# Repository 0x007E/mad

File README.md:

# `MAD` - Matrix Display

The `MAD` project is based on a pcb with an [ATtiny406/ATtiny1606](#additional-information) and a [Matrix LED Display](#additional-information). It can be used to display data sent over `SPI` or `UART`. The display also implements a small amount of characters from the ASCII table and also has internal space (`EEPROM`) for 16 special characters that can be programmed.

| Experience | Level |
|:------------|:-----:|
| Soldering   |  |
| Mechanical  |  |
| Software    |  |

# Downloads

| Type      | File               | Description              |
|:---------:|:------------------:|:-------------------------|
| Schematic | [pdf](https://github.com/0x007E/mad/releases/latest/download/schematic.pdf) / [cadlab](https://cadlab.io/project/28600/main/files) | Schematic files |
| Board | [pdf](https://github.com/0x007E/mad/releases/latest/download/pcb.pdf) / [cadlab](https://cadlab.io/project/28600/main/files) | Board file |
| Drill | [pdf](https://github.com/0x007E/mad/releases/latest/download/drill.pdf) | Drill file |
| PCB | [zip](https://github.com/0x007E/mad/releases/latest/download/kicad.zip) / [tar](https://github.com/0x007E/mad/releases/latest/download/kicad.tar.gz) | KiCAD/Gerber/BoM/Drill files |
| Mechanical | [zip](https://github.com/0x007E/mad/releases/latest/download/freecad.zip) / [tar](https://github.com/0x007E/mad/releases/latest/download/freecad.tar.gz) | FreeCAD/Housing and PCB (STEP) files     |
| Firmware | [zip](https://github.com/0x007E/mad/releases/latest/download/firmware.zip) / [tar](https://github.com/0x007E/mad/releases/latest/download/firmware.tar.gz) | Firmware for ATtiny406/ATtiny1606 (Display) |
| Firmware (demo) | [zip](https://github.com/0x007E/mad/releases/latest/download/firmware-demo.zip) / [tar](https://github.com/0x007E/mad/releases/latest/download/firmware-demo.tar.gz) | Test application(s) for ATmega16a |

# Hardware

There are two parts of the hardware. The pcb and the housing of the `MAD`. The pcb is created with [KiCAD](#additional-information) and the housing with `FreeCAD`. The software is programmed with [Microchip (Atmel) Studio](#additional-information). All files are built with `github actions` so that they are ready for a production environment. The housing is printed with a 3D-printer (`Dremel 3D40`).

## PCB

The circuit board is populated on both sides (Top, Bottom). The best way for soldering the `SMD` components is within a vapor phase soldering system and for the `THT` components with a standard soldering system.

### Top Layer

### Bottom Layer

## Mechanical

The housing has a tolerance of `0.2mm` on each side of the case. So the pcb should fit perfectly in the housing. The tolerance can be modified with `FreeCAD` in the `Parameter` Spreadsheet.

### Assembled

#### Exploded

# Programming/Setup

The `MAD` is powerd with `5V` from an external source. With Jumper `JP1` bridged the `MAD` can be programmed over [UPDI](#additional-information). To enable `UART` mode the `SS (CS)` Pin must be held low (more details on the [dataflow](#dataflow-diagram) diagram) otherwise the `SPI` mode is enabled. In `UART` mode only one display can be driven. The `SI` pin gets `TXD`and the `SO` pin gets `RXD`. The firmware for the display can be downloaded (see the [download section](#downloads)).

``` bash
#         +-+                                         +----------+      +---------------------+
#        / /                                          |   U  +---+---+  |                     |
#      +-+-+-----------------+                        |   S  |  USB  |--+ +-----------------+ |
#      | JP1                 |                        |   B  +---+---+  | | AVR-Dude        | |
#      |    MAD - Display    |       +---------+      |   /      |      | | ~~~~~~~~        | |
#    +-+-+                 +-+-+   +-+-+  U    |      |   U      |      | | ~~~~~           | |
#    | 1 | VCC         VCC | 1 +---+VCC|  P  +-+-+  +-+-+ A      |      | | ~~~~~~~~~~~~    | |
#    | 2 | UPDI       UPDI | 2 +---+PDI|  D  |GND+--+GND| R      |      | |                 | |
#    | 3 | SI           SO | 3 |   +-+-+  I  |VCC+--+VCC| T      |      | +-----------------+ |
#    | 4 | SCK         SCK | 4 |     |       +---+  +---+ A      |      |                     |
#    | 5 | SS (CS)      SS | 5 +   +-+-+     |RxD+--+RxD| +------+      | Computer            |
#    | 6 | GND         GND | 6 +---+GND|     |TxD+--+TxD| |5V/3V3|      |                     |
#    +-+-+                 +-+-+   +-+-+     +-+-+  +-+-+ +------+      +---------------------+
#      +---------------------+       | ADAPTER |      +----+-----+
#                                    +---------+
```

## FUSES

| Register  | Value  |
|:---------:|:------:|
| `WDTCFG`  | `0x00` |
| `BODCFG`  | `0x00` |
| `OSCCFG`  | `0x02` |
| `TCD0CFG` | `0x00` |
| `SYSCFG0` | `0xF5` |
| `SYSCFG1` | `0x00` |
| `APPEND`  | `0x00` |
| `BOOTEND` | `0x00` |

> To setup `SW1` as `RESET` (`PA0`) it is necessary to change the `SYSCFG0`-FUSE of the `ATtiny406/ATtiny1606`. WARNING: To reset the `PA0` pin to `UPDI` mode a `12V` impulse is necessary to program the FUSES again.

# Software

The display software can be controlled by `SPI` or `UART`. The interfaces are displayed in the [dataflow](#dataflow-diagram) diagram. There is a demo software to use the display directly over `spi` (`MAD_Test`) or a `library` (`MAD_LIB`).

## Dataflow diagram

## UART Test

To send characters to the display over `UART` connect an USB/UART converter to the PC and make a bridge beween `GND` and `SS (CS)` before powering up the display. Start a terminal software on the computer (e.g. [Teraterm](#additional-information)) and setup the following settings:

| Name      | Value  |
|:---------:|:------:|
| PORT      | COM?   |
| BAUD      | 9600   |
| DATABITS  | 8      |
| PARITY    | NONE   |
| STOPBITS  | 1      |
| FLOWCTRL  | NONE   |

### Connection setup

``` bash

#      +---------------------+                                +---------------------+
#      |    MAD - Display    |                                |                     |
#    +-+-+                 +-+-+                              | +-----------------+ |
#    | 1 | VCC         VCC | 1 +-------+    +----------+      | | TeraTerm        | |
#    | 2 | UPDI       UPDI | 2 |       |    |   U  +---+---+  | | ~~~~~~~~        | |
#    | 3 | SI           SO | 3 +-----+ |    |   S  |  USB  |--+ | ~~~~~           | |
#    | 4 | SCK         SCK | 4 |     | |    |   B  +---+---+  | | ~~~~~~~~~~~~    | |
#    | 5 | SS (CS)      SS | 5 +--+  | |    |   /      |      | |                 | |
# +--+ 6 | GND         GND | 6 +--+  | |    |   U      |      | +-----------------+ |
# |  +-+-+                 +-+-+     | |  +-+-+ A      |      |                     |
# |    +---------------------+       | +--+VCC| R      |      | Computer            |
# |                                  +----+TxD| T      |      |                     |
# |                                       |RxD| +------+      +---------------------+
# +---------------------------------------+GND| |5V/3V3|
#                                         +-+-+ +------+
#                                           +----+-----+
```

## SPI Test

The `firmware` itself contains some demos how to use the display over `spi`. The demo software itself is written for an [ATmega16A](#additional-information). To test the display a connection to the `spi` pins between the display and the [ATmega16A](#additional-information)is necessary.

### Connection setup

``` bash
# ~------------+
# ~          +-+-+
# ~          |VCC+------+
# ~          +-+-+       \        +---------------------+
# ~            |          \       |     MAD - Display   |
# ~  A       +-+-+         \    +-+-+                 +-+-+
# ~  T   [7] | P +- SCK -+  +---+ 1 | VCC         VCC | 1 |
# ~  M       | O |        \     | 2 | UPDI       UPDI | 2 |
# ~  E       | R +- MOSI --\----+ 3 | SI           SO | 3 |
# ~  G       | T +-- SS -+  +---+ 4 | SCK         SCK | 4 |
# ~  A       | B |       +------+ 5 | SS (CS)      SS | 5 |
# ~          |   |           +--+ 6 | GND         GND | 6 |
# ~  1       |   |          /   +-+-+                 +-+-+
# ~  6   [0] |   |         /      |                     |
# ~  A       +-+-+        /       +---------------------+
# ~            |         /
# ~          +-+-+      /
# ~          |GND+-----+
# ~          +-+-+
# ~~~~~~~~~~~~~~ 
```

### SPI Parameter

To control the display through `SPI` the bus of the master needs the following setup:

| Parameter | Value   | Description |
|:----------|:-------:|:------------|
| Clock     | < 1Mhz  | Bus clock speed should not exceed this value |
| Direction | MSB     | MSB needs to be transmitted first |
| Polarity  | Rising  | Polarity of clock is rising `_/` |
| Phase     | Rising  | Data is valid when clock is rising `_/` |

> Detail can be found [here](https://de.wikipedia.org/wiki/Serial_Peripheral_Interface)

### SPI Frame

``` bash

# SPI display transmission
# _                                                SS                                                _
#  \________________________________________________________________________________________________/
#                                                 SCK   
#     __    __    __    __    __    __    __    __    __    __    __    __    __    __    __    __    
# ___/1 \__/2 \__/3 \__/4 \__/5 \__/6 \__/7 \__/8 \__/9 \__/10\__/11\__/12\__/13\__/14\__/15\__/16\___
#                                                 MOSI
#    __    __    __    __    __    __    __    __    __    __    __    __    __    __    __    __
# __/C \__/T \__/R \__/L \__/B \__/Y \__/T \__/E \__/D \__/A \__/T \__/A \__/B \__/Y \__/T \__/E \____
#   \__/  \__/  \__/  \__/  \__/  \__/  \__/  \__/  \__/  \__/  \__/  \__/  \__/  \__/  \__/  \__/
#    [7                   :                    0]    [7                   :                    0]
```

### SPI Commands

To enable a bit it needs to be set to on ($1=ON$). To disable a bit it is necessary to set it to off ($0=OFF$).

| Control-Byte | Data-Bit(s)| Description    |
|:------------:|:----------:|:---------------|
| `0x00`       | `0xXX`     | No operation   | 
| `0x01`       | `[4:0]`    | ROW1 LEDs | 
| ...          | ...        | ... | 
| `0x07`       | `[4:0]`    | ROW7 LEDs | 
| `0x08`       | `[6:0]`    | Show ASCII character on display |
| `0x10`       | `0xXX`    | Clear buffer |
| `0x1F`       | `[0]`      | Enable display |
| `0x20`       | `0xXX`     | Copy EEPROM address (0) to display |
| ...          | ...        | ... | 
| `0x2F`       | `0xXX`     | Copy EEPROM address (15) to display |
| `0x30`       | `0xXX`     | Copy Display content to EEPROM address (0) |
| ...          | ...        | ... | 
| `0x3F`       | `0xXX`     | Copy Display content to EEPROM address (15) |
| `0xF0`       | `0xXX`     | Display refresh rate LOW byte |
| `0xF1`       | `0xXX`     | Display refresh rate HIGH byte |
| `0xFF`       | `0xXX`     | RESET the SPI queue |

### Example Library (`matrix.h`)

With the attached demo library (`MAD_LIB`) it is quiet easy to use the display. To setup the matrix display library some `defines` needs to be adjusted.

``` c
// Setup the number of displays that are cascaded
#ifndef MATRIX_DISPLAYS
    #define MATRIX_DISPLAYS 2
#endif
```

``` c
#include "../lib/matrix/matrix.h"

int main(void)
{
    matrix_init();
    matrix_reset();
    _delay_ms(MATRIX_RESET_RECOVERY_TIME_MS);
    matrix_enable();

    matrix_char(1, 'A');
    _delay_ms(1000);
    matrix_char(2, 'B');

    matrix_frame(buffer);
    // ...
}
```

# Additional Information

| Type       | Link               | Description              |
|:----------:|:------------------:|:-------------------------|
| ATtiny406  | [pdf](https://ww1.microchip.com/downloads/en/DeviceDoc/Microchip%208bit%20mcu%20AVR%20ATtiny406%20data%20sheet%2040001976A.pdf) | ATtiny microcontroller |
| ATtiny1606 | [pdf](http://ww1.microchip.com/downloads/en/DeviceDoc/ATtiny806_1606_Data_Sheet_40002029A.pdf) | ATtiny microcontroller |
| ATmega16A | [pdf](https://ww1.microchip.com/downloads/en/devicedoc/atmel-8154-8-bit-avr-atmega16a_datasheet.pdf) | Microchip ATmega16A Datasheet |
| TA20-11SRWA | [pdf](https://www.kingbrightusa.com/images/catalog/spec/ta20-11srwa.pdf) | Dot Matrix Dispaly |
| Atmel ICE | [pdf](https://ww1.microchip.com/downloads/en/DeviceDoc/Atmel-ICE_UserGuide.pdf) | Atmel ICE datasheet |
| UPDI | [web](https://github.com/0x007e/updi) | UPDI-Adapter with AVR-Dude |
| Microchip Studio | [web](https://www.microchip.com/en-us/tools-resources/develop/microchip-studio) | Download page for Microchip Studio |
| KiCAD | [web](https://www.kicad.org/) | KiCAD project page |
| FreeCAD | [web](https://www.freecad.org/) | FreeCAD project page |
| TeraTerm | [web](https://github.com/TeraTermProject/teraterm/releases/download/v5.3/teraterm-5.3.zip) | Terminal software for UART |

---

R. GAECHTER

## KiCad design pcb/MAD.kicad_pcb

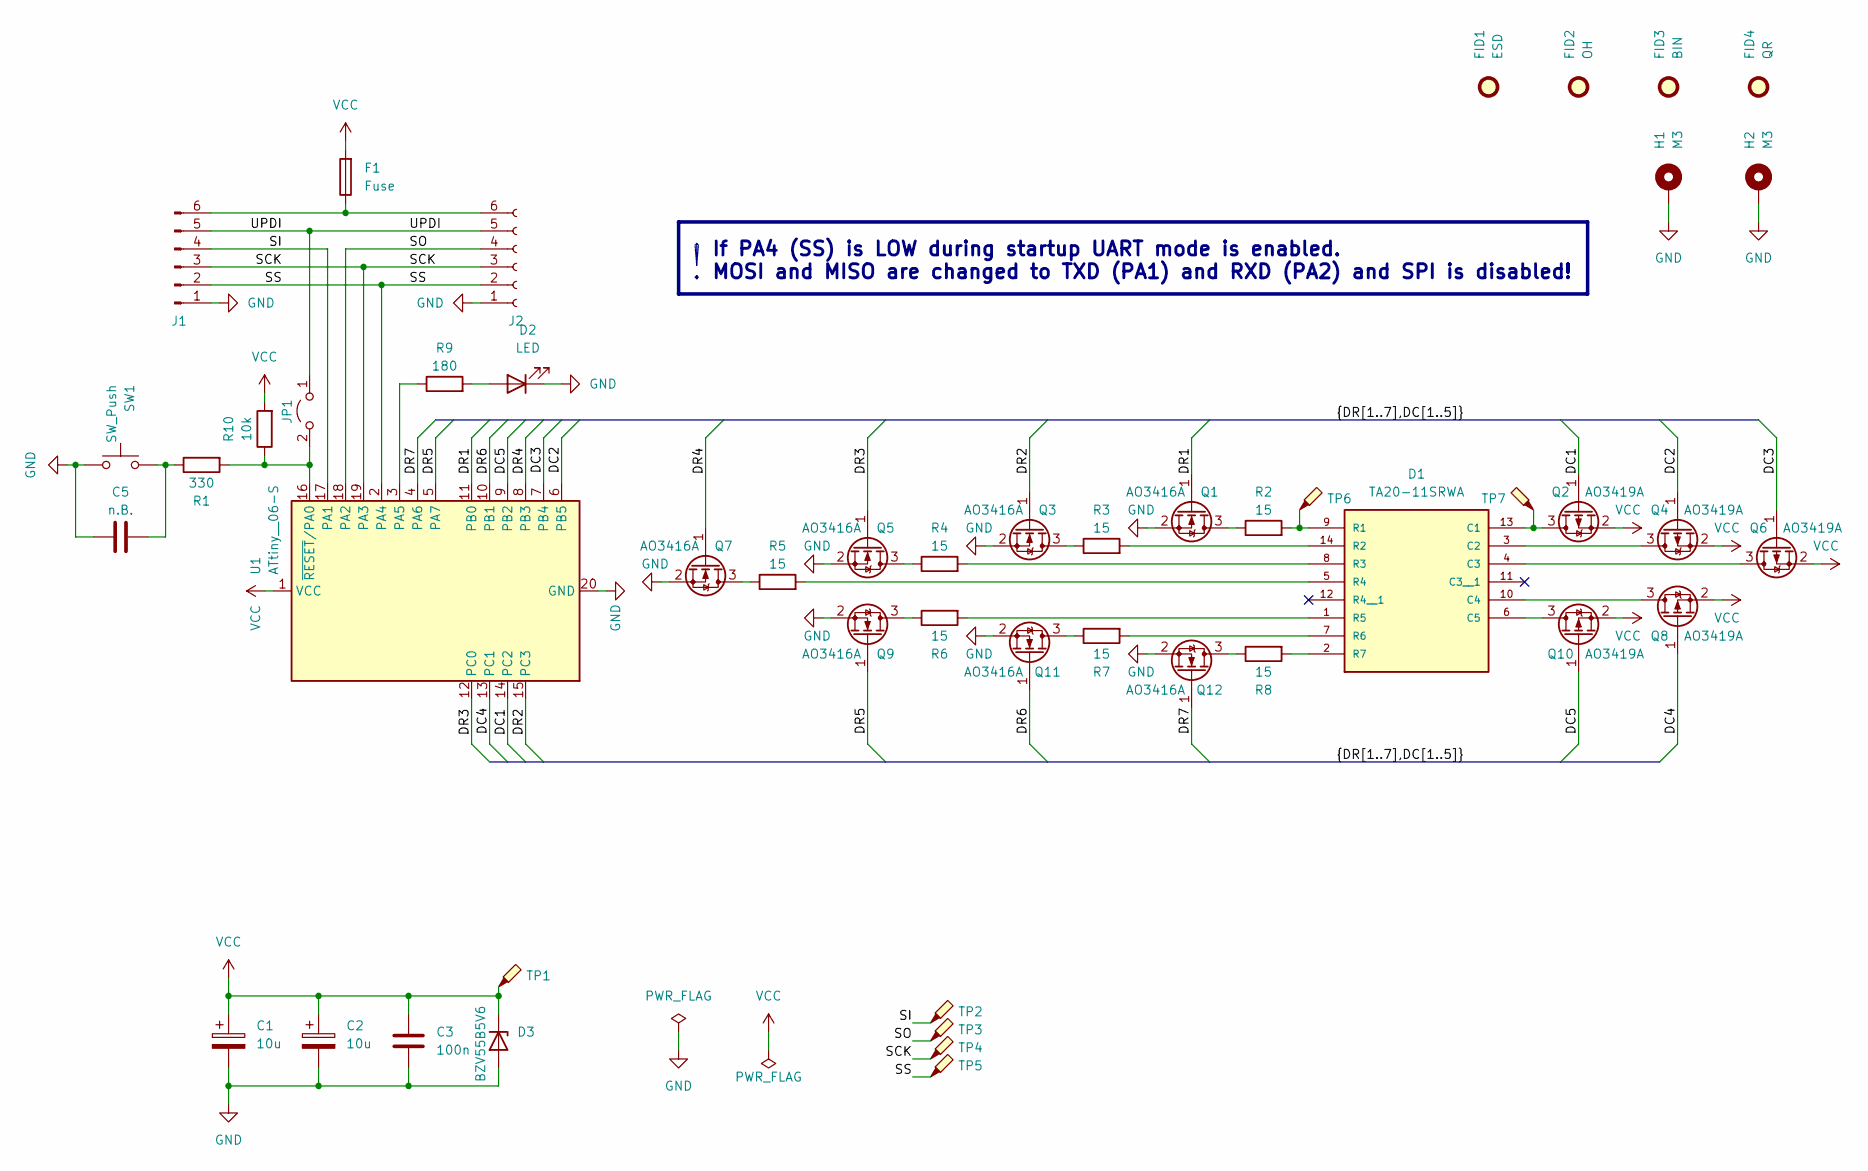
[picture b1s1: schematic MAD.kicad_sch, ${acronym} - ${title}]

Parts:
C1, C2: 10u; CP_EIA-6032-28_Kemet-C
C3: 100n; C_1206_3216Metric
C5: n.B.; C_1206_3216Metric
D1: TA20-11SRWA; LED_TA20-11SRWA
D2: LED; LED_1206_3216Metric
D3: BZV55B5V6; D_MiniMELF
F1: Fuse; Fuse_1206_3216Metric
FID1: ESD; ESD-Logo_6.6x6mm_SilkScreen
FID2: OH; OSHW-Logo_5.7x6mm_SilkScreen
FID3: BIN; WEEE-Logo_4.2x6mm_SilkScreen
FID4: QR; QR_0x007e
H1, H2: M3; MountingHole_3.2mm_M3_DIN965_Pad
J1: Conn_01x06_Pin; PinHeader_1x06_P2.54mm_Horizontal
J2: Conn_01x06_Socket; PinSocket_1x06_P2.54mm_Horizontal
JP1: Jumper_2_Open; PinHeader_1x02_P2.54mm_Horizontal
Q1, Q3, Q5, Q7, Q9, Q11, Q12: AO3416A; SOT-23
Q2, Q4, Q6, Q8, Q10: AO3419A; SOT-23
R1: 330; R_1206_3216Metric
R2, R3, R4, R5, R6, R7, R8: 15; R_1206_3216Metric
R9: 180; R_1206_3216Metric
R10: 10k; R_1206_3216Metric
SW1: SW_Push; SW_SPST_PTS645
TP1, TP2, TP3, TP4, TP5, TP6, TP7: TestPoint_Probe; TestPoint_Pad_D1.0mm
U1: ATtiny__06-S; SOIC-20W_7.5x12.8mm_P1.27mm

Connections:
/DC1: Q2.1 (G), U1.14 (PC2)
/DC2: Q4.1 (G), U1.6 (PB5)
/DC3: Q6.1 (G), U1.7 (PB4)
/DC4: Q8.1 (G), U1.13 (PC1)
/DC5: Q10.1 (G), U1.9 (PB2)
/DR1: Q1.1 (G), U1.11 (PB0)
/DR2: Q3.1 (G), U1.15 (PC3)
/DR3: Q5.1 (G), U1.12 (PC0)
/DR4: Q7.1 (G), U1.8 (PB3)
/DR5: Q9.1 (G), U1.5 (PA7)
/DR6: Q11.1 (G), U1.10 (PB1)
/DR7: Q12.1 (G), U1.4 (PA6)
/SCK: J1.3, J2.3, TP4.1, U1.19 (PA3)
/SI: J1.4, TP2.1, U1.17 (PA1)
/SO: J2.4, TP3.1, U1.18 (PA2)
/SS: J1.2, J2.2, TP5.1, U1.2 (PA4)
/UPDI: J1.5, J2.5, JP1.1 (A)
GND: C1.2, C2.2, C3.2, C5.2, D2.1 (K), D3.2 (A), H1.1, H2.1, J1.1, J2.1, Q1.2 (S), Q3.2 (S), Q5.2 (S), Q7.2 (S), Q9.2 (S), Q11.2 (S), Q12.2 (S), SW1.1, U1.20 (GND)
unnamed: C5.1, R1.1, SW1.2
unnamed: D1.13 (C1), Q2.3 (D), TP7.1
unnamed: D1.3 (C2), Q4.3 (D)
unnamed: D1.4 (C3), Q6.3 (D)
unnamed: D1.10 (C4), Q8.3 (D)
unnamed: D1.6 (C5), Q10.3 (D)
unnamed: D1.9 (R1), R2.2, TP6.1
unnamed: D1.14 (R2), R3.2
unnamed: D1.8 (R3), R4.2
unnamed: D1.5 (R4), R5.2
unnamed: D1.1 (R5), R6.2
unnamed: D1.7 (R6), R7.2
unnamed: D1.2 (R7), R8.2
unnamed: D2.2 (A), R9.2
unnamed: F1.1, J1.6, J2.6
unnamed: JP1.2 (B), R1.2, R10.1, U1.16 (~RESET/PA0)
unnamed: Q1.3 (D), R2.1
unnamed: Q3.3 (D), R3.1
unnamed: Q5.3 (D), R4.1
unnamed: Q7.3 (D), R5.1
unnamed: Q9.3 (D), R6.1
unnamed: Q11.3 (D), R7.1
unnamed: Q12.3 (D), R8.1
unnamed: R9.1, U1.3 (PA5)
VCC: C1.1, C2.1, C3.1, D3.1 (K), F1.2, Q2.2 (S), Q4.2 (S), Q6.2 (S), Q8.2 (S), Q10.2 (S), R10.2, TP1.1, U1.1 (VCC)

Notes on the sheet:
If PA4 (SS) is LOW during startup UART mode is enabled. MOSI and MISO are changed to TXD (PA1) and RXD (PA2) and SPI is disabled!

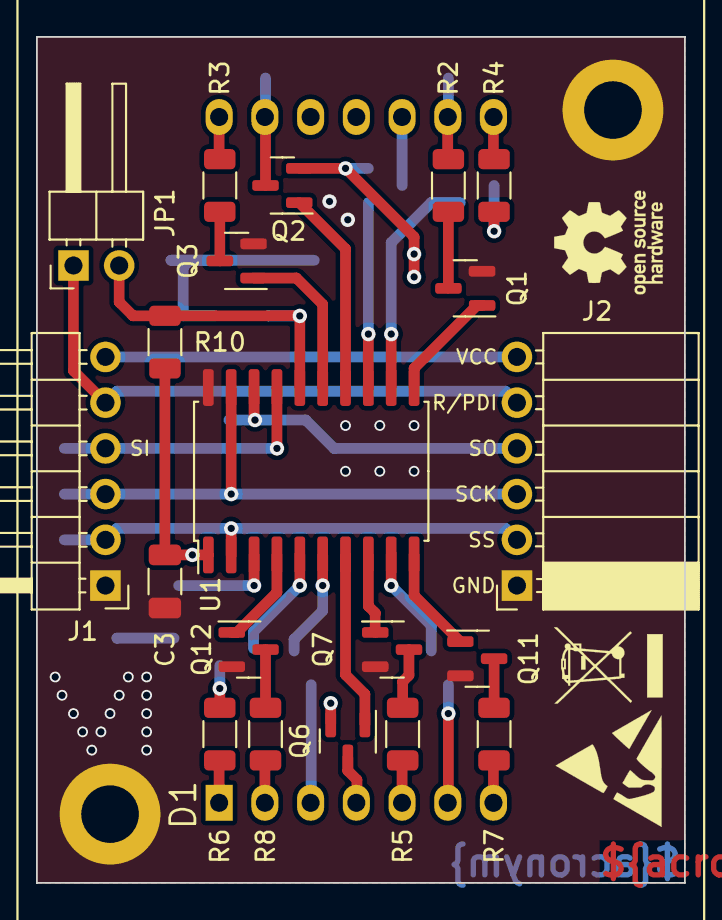
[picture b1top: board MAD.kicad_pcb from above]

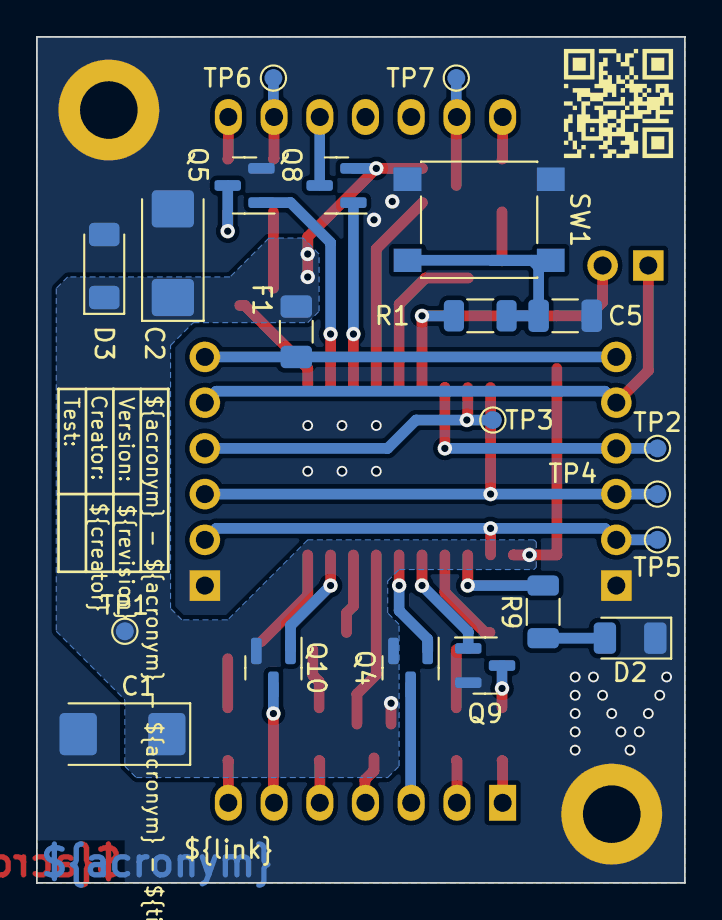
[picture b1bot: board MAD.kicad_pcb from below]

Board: 2 copper layers, 36.0 x 47.0 mm, 48 parts (22 on the bottom side), 43 nets.

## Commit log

2024-10-25 Add README
2024-10-25 Create pipeline
2024-10-25 Fix wrong device
2024-10-25 Fix wrong DFP
2024-10-25 Fix wrong path
2024-10-25 Fix pin name
2024-10-25 Change config
2024-10-25 Fix broken links
2024-11-22 Optimize resistor values
2024-11-22 Rearrange fabrication text
2024-11-22 Change SPI-Bus names
2024-11-22 Add ATtiny __06 to design
2024-11-22 Add ATtiny1606 to README
2024-11-22 Rename SPI-Bus names
2024-11-22 Add image for preview
2024-11-22 Add comments/optimize code
2024-11-22 Add missing SPI-Command
2024-11-22 Fix SPI direction
2024-11-22 Add ATtiny1606 to firmware
2024-11-23 Change dataword
2024-11-23 Change delay
2024-11-25 Fix number in partlist
2024-11-26 Change scaling
2024-11-27 Add mounting screw
2024-11-27 Add values to partlist
2024-11-29 Change SPI speed
2024-11-29 Remove hard-coded lines
2024-12-01 Move code dependencies
2024-12-01 Activate signaling LED
2024-12-01 Code cleanup
2024-12-02 Change test time
2024-12-02 Fix UART
2024-12-02 Allow only capital ASCII-letters
2024-12-02 Modifiy ASCII characters
2024-12-02 Add ASCII characters
2024-12-02 Modifiy ASCII numbers
2024-12-02 Catch address over-/underflow
2024-12-02 Change UART connection setup
2024-12-02 Fix wrong connection
2024-12-04 Swapped column/row algorithm
2024-12-04 Add note
2024-12-04 Add option to disable status led
2024-12-06 Change refresh rate
2024-12-06 Optimize current consumption
2025-02-04 Activate TA20 in 3D-View
2025-02-04 Rename download parts
2025-02-04 Fix mirroring
2025-02-04 Add housing to artifacts
2025-02-04 Update/Add diagrams at programming section
2025-02-04 Enable SPACE transmission
2025-02-04 Update programming diagram
2025-03-26 Pull SS HIGH to prevent UART mode
2025-09-13 Code refactoring
2025-09-13 Increase FreeCAD version
2025-10-24 Change pipeline badge to release.yml
2025-10-24 Change firmware pipeline
2025-10-29 Add DeepWiki badge

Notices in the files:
README.md:
License CC By-NC-SA
parts and their libraries:
license: CC BY-NC-SA 4.0
